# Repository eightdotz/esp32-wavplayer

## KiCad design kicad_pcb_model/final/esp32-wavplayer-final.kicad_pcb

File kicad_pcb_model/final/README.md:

# Parts List  
  
# LCSC:  
  
MicroSD Module: JBL JBL-102010052 | 9 pin SD card (one detect pin)  
Display: Wise Vision X096-2864KSWPG01-H30 | SSD1315 Display Driver  
Audio Driver: TI PCM5102APWR  
Voltage Regulator for Display: XC6206P332MR-G  
Buttons: OMRON B3U-1000P | SMD buttons  
Battery Controller: TP4096 | 1a of charging current is fine for this application.  
For higher current charging, try the Consonance CN3791  
  
Audio Jack: KHE PJ-332A-6A  
  
# DigiKey:  
  
USB-C Jack: 2223-UJ20-C-H-G-SMT-1-P16-TRCT-ND | 16 pin USB-C port. 2073-USB4125-GF-ACT-ND is the 6 pin alternative  
CPU: ESP32-C3 (1904-ESP32-C3CT-ND)

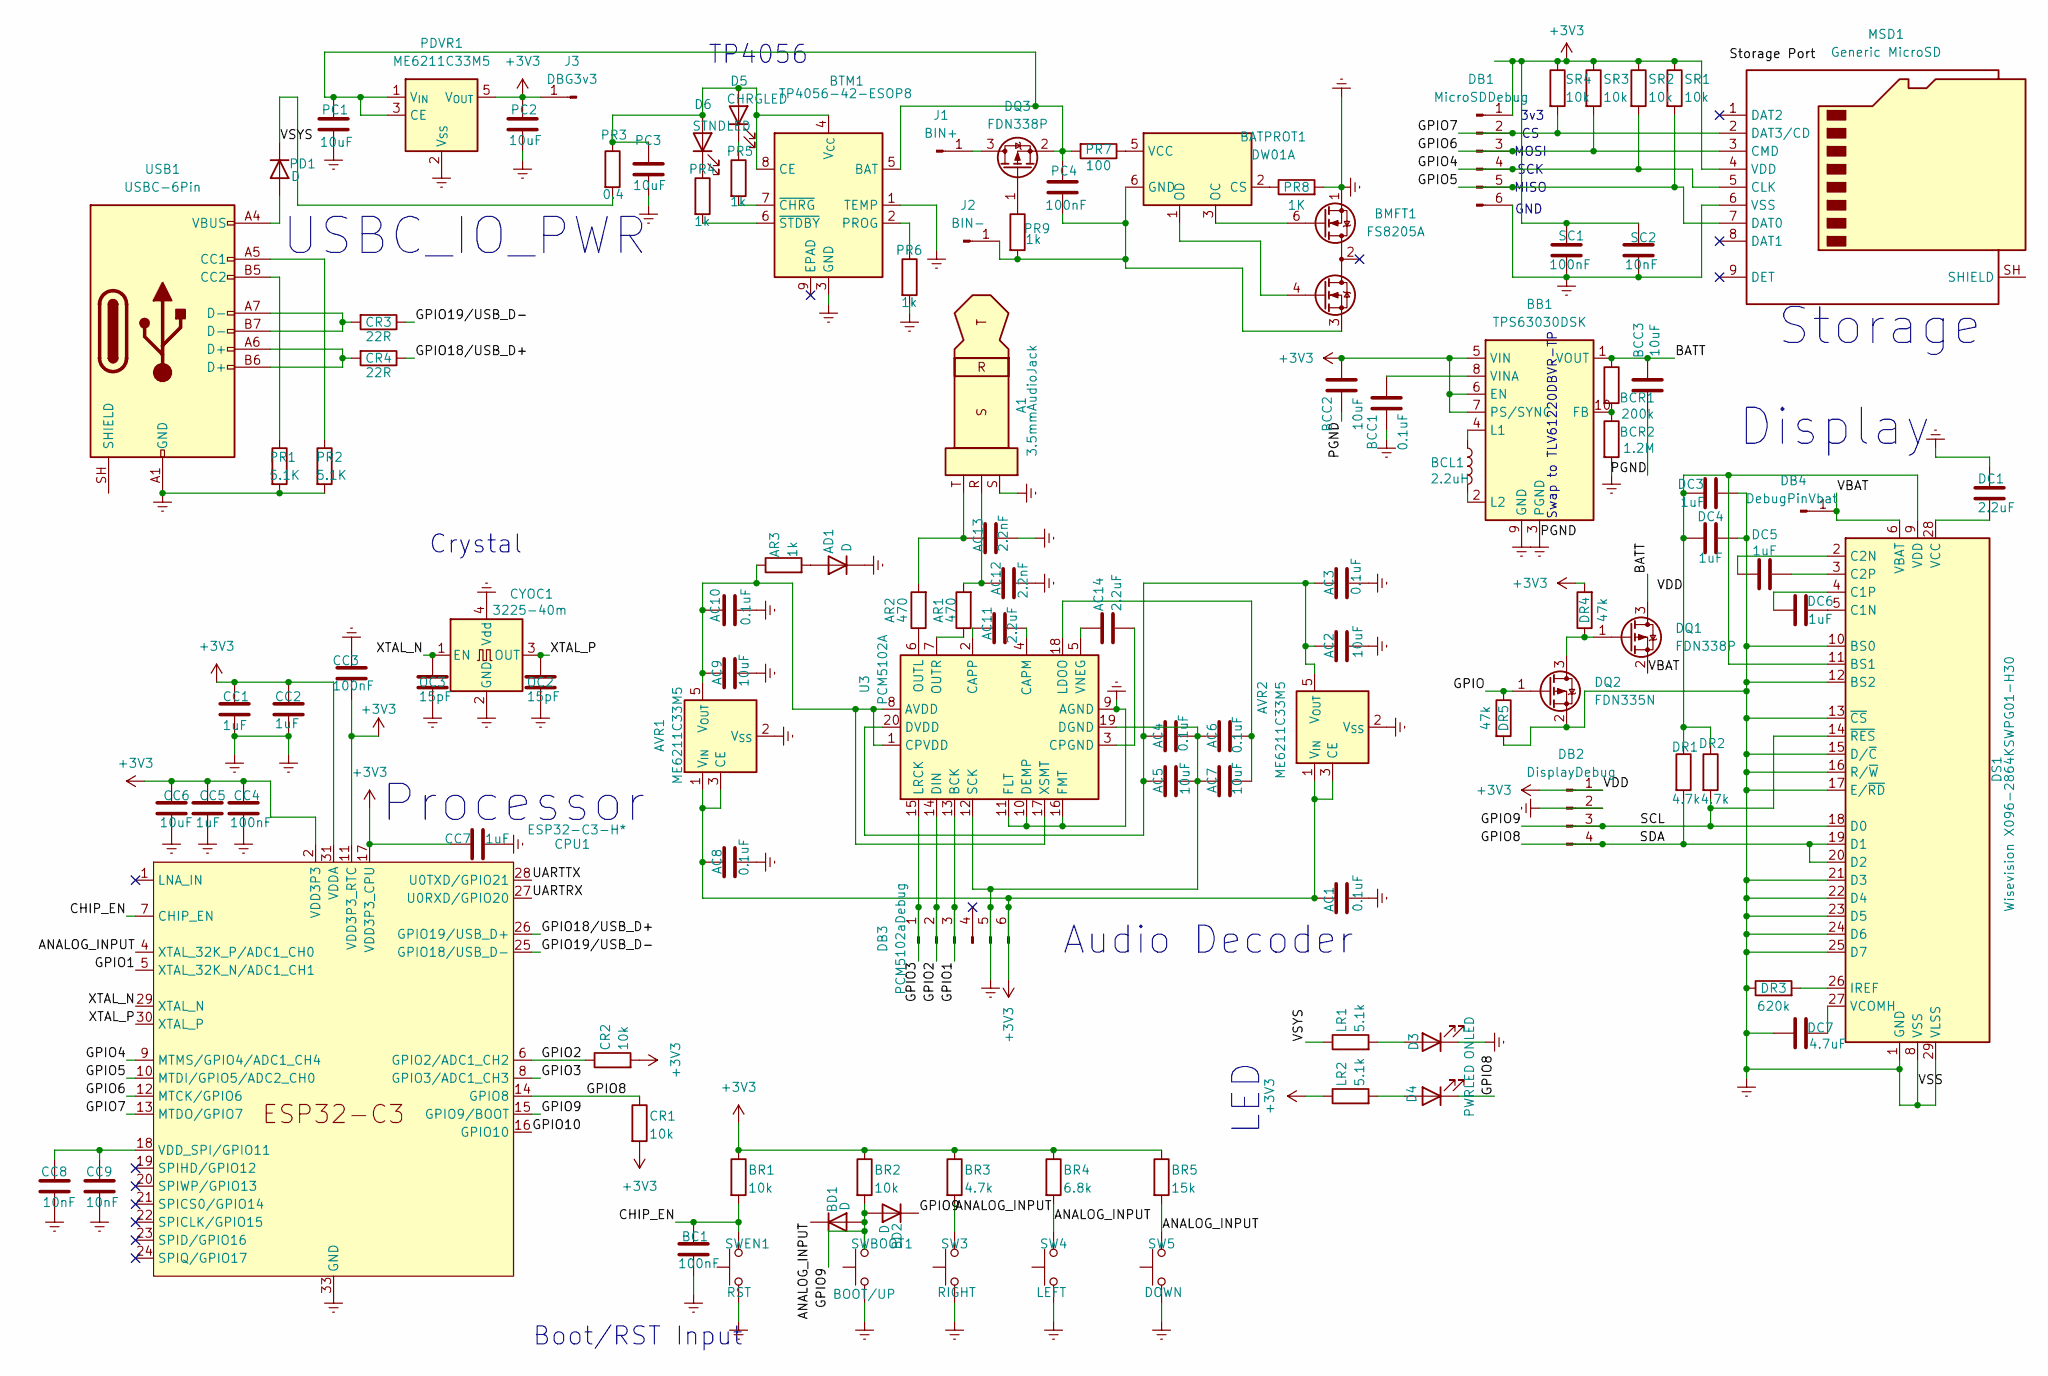
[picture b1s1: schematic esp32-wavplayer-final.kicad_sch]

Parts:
A1: 3.5mmAudioJack; Jack_3.5mm_KoreanHropartsElec_PJ-320D-4A_Horizontal
AC1, AC3, AC4, AC6, AC8, AC10: 0.1uF; C_0603_1608Metric_Pad1.08x0.95mm_HandSolder
AC2, AC5, AC7, AC9: 10uF; C_0603_1608Metric_Pad1.08x0.95mm_HandSolder
AC11, AC14: 2.2uF; C_0603_1608Metric_Pad1.08x0.95mm_HandSolder
AC12, AC13: 2.2nF; C_0603_1608Metric_Pad1.08x0.95mm_HandSolder
AD1: D; D_0603_1608Metric_Pad1.05x0.95mm_HandSolder
AR1, AR2: 470; R_0603_1608Metric_Pad0.98x0.95mm_HandSolder
AR3: 1k; R_0603_1608Metric_Pad0.98x0.95mm_HandSolder
AVR1, AVR2: ME6211C33M5; SOT-23-5
BATPROT1: DW01A; SOT-23-6
BB1: TPS63030DSK; WSON-10-1EP_2.5x2.5mm_P0.5mm_EP1.2x2mm
BC1: 100nF; C_0603_1608Metric_Pad1.08x0.95mm_HandSolder
BCC1: 0.1uF; C_0603_1608Metric_Pad1.08x0.95mm_HandSolder
BCC2, BCC3: 10uF; C_0603_1608Metric_Pad1.08x0.95mm_HandSolder
BCL1: 2.2uH; L_0201_0603Metric_Pad0.64x0.40mm_HandSolder
BCR1: 200k; R_0603_1608Metric_Pad0.98x0.95mm_HandSolder
BCR2: 1.2M; R_0603_1608Metric_Pad0.98x0.95mm_HandSolder
BD1, BD2: D; D_0603_1608Metric_Pad1.05x0.95mm_HandSolder
BMFT1: FS8205A; SOT-23-6
BR1, BR2: 10k; R_0603_1608Metric_Pad0.98x0.95mm_HandSolder
BR3: 4.7k; R_0603_1608Metric_Pad0.98x0.95mm_HandSolder
BR4: 6.8k; R_0603_1608Metric_Pad0.98x0.95mm_HandSolder
BR5: 15k; R_0603_1608Metric_Pad0.98x0.95mm_HandSolder
BTM1: TP4056-42-ESOP8; SOIC-8_3.9x4.9mm_P1.27mm
CC1, CC2, CC5, CC7: 1uF; C_0603_1608Metric_Pad1.08x0.95mm_HandSolder
CC3, CC4: 100nF; C_0603_1608Metric_Pad1.08x0.95mm_HandSolder
CC6: 10uF; C_0603_1608Metric_Pad1.08x0.95mm_HandSolder
CC8, CC9: 10nF; C_0603_1608Metric_Pad1.08x0.95mm_HandSolder
CPU1: ESP32-C3-H*; QFN-32-1EP_5x5mm_P0.5mm_EP3.45x3.45mm
CR1, CR2: 10k; R_0603_1608Metric_Pad0.98x0.95mm_HandSolder
CR3, CR4: 22R; R_0603_1608Metric_Pad0.98x0.95mm_HandSolder
CYOC1: 3225-40m; Oscillator_SMD_Abracon_ASE-4Pin_3.2x2.5mm
D3: PWRLED; LED_0603_1608Metric_Pad1.05x0.95mm_HandSolder
D4: ONLED; LED_0603_1608Metric_Pad1.05x0.95mm_HandSolder
D5: CHRGLED; LED_0603_1608Metric_Pad1.05x0.95mm_HandSolder
D6: STNDLED; LED_0603_1608Metric_Pad1.05x0.95mm_HandSolder
DB1: MicroSDDebug; PinHeader_1x06_P2.54mm_Vertical
DB2: DisplayDebug; PinHeader_1x04_P2.54mm_Vertical
DB3: PCM5102aDebug; PinHeader_1x06_P2.54mm_Vertical
DB4: DebugPinVbat; PinHeader_1x01_P2.54mm_Vertical
DC1: 2.2uF; C_0603_1608Metric_Pad1.08x0.95mm_HandSolder
DC3, DC4, DC5, DC6: 1uF; C_0603_1608Metric_Pad1.08x0.95mm_HandSolder
DC7: 4.7uF; C_0603_1608Metric_Pad1.08x0.95mm_HandSolder
DQ1, DQ3: FDN338P; SOT-23
DQ2: FDN335N; SOT-23
DR1, DR2: 4.7k; R_0603_1608Metric_Pad0.98x0.95mm_HandSolder
DR3: 620k; R_0603_1608Metric_Pad0.98x0.95mm_HandSolder
DR4, DR5: 47k; R_0603_1608Metric_Pad0.98x0.95mm_HandSolder
DS1: Wisevision X096-2864KSWPG01-H30; OLED-128O064D
J1: BIN+; PinHeader_1x01_P2.54mm_Vertical
J2: BIN-; PinHeader_1x01_P2.54mm_Vertical
J3: DBG3v3; PinHeader_1x01_P2.54mm_Vertical
LR1, LR2: 5.1k; R_0603_1608Metric_Pad0.98x0.95mm_HandSolder
MSD1: Generic MicroSD; microSD_HC_Hirose_DM3AT-SF-PEJM5
OC2, OC3: 15pF; C_0603_1608Metric_Pad1.08x0.95mm_HandSolder
PC1, PC2, PC3: 10uF; C_0603_1608Metric_Pad1.08x0.95mm_HandSolder
PC4: 100nF; C_0603_1608Metric_Pad1.08x0.95mm_HandSolder
PD1: D; D_0603_1608Metric_Pad1.05x0.95mm_HandSolder
PDVR1: ME6211C33M5; SOT-23-5
PR1, PR2: 5.1K; R_0603_1608Metric_Pad0.98x0.95mm_HandSolder
PR3: 0.4; R_0603_1608Metric_Pad0.98x0.95mm_HandSolder
PR4, PR5, PR6, PR9: 1k; R_0603_1608Metric_Pad0.98x0.95mm_HandSolder
PR7: 100; R_0603_1608Metric_Pad0.98x0.95mm_HandSolder
PR8: 1K; R_0603_1608Metric_Pad0.98x0.95mm_HandSolder
SC1: 100nF; C_0603_1608Metric_Pad1.08x0.95mm_HandSolder
SC2: 10nF; C_0603_1608Metric_Pad1.08x0.95mm_HandSolder
SR1, SR2, SR3, SR4: 10k; R_0603_1608Metric_Pad0.98x0.95mm_HandSolder
SW3: RIGHT; SW_SPST_TS-1088-xR020
SW4: LEFT; SW_SPST_TS-1088-xR020
SW5: DOWN; SW_SPST_TS-1088-xR020
SWBOOT1: BOOT/UP; SW_SPST_TS-1088-xR020
SWEN1: RST; SW_SPST_TS-1088-xR020
U3: PCM5102A; TSSOP-20_4.4x6.5mm_P0.65mm
USB1: USBC-6Pin; USB_C_Receptacle_HRO_TYPE-C-31-M-12

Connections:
+3V3: AC1.1, AC8.1, AVR1.1 (V_{IN}), AVR1.3 (CE), AVR2.1 (V_{IN}), AVR2.3 (CE), BB1.5 (VIN), BB1.6 (EN), BB1.7 (PS/SYNC), BCC2.2, BR1.1, BR2.1, BR3.1, BR4.1, BR5.1, CC1.1, CC2.1, CC3.2, CC4.1, CC5.1, CC6.1, CC7.1, CPU1.2 (VDD3P3), CPU1.3 (VDD3P3), CPU1.11 (VDD3P3_RTC), CPU1.17 (VDD3P3_CPU), CPU1.31 (VDDA), CPU1.32 (VDDA), CR1.2, CR2.2, DB1.1, DB2.1, DB3.6, DC3.1, DC4.2, DR1.1, DR2.1, DR4.2, DS1.9 (VDD), DS1.11 (BS1), J3.1 (Pin_1_1), LR2.1, MSD1.4 (VDD), PC2.1, PDVR1.5 (V_{OUT}), SC1.1, SC2.1, SR1.1, SR2.1, SR3.1, SR4.1
/ANALOG_INPUT: BD1.1 (K), BR3.2, BR4.2, BR5.2, CPU1.4 (XTAL_32K_P/ADC1_CH0), SW3.2, SW4.2, SW5.2
/BATT: BB1.1 (VOUT), BCC3.2, BCR1.1, DQ1.3 (D)
/CHIP_EN: BC1.1, BR1.2, CPU1.7 (CHIP_EN), SWEN1.2; also elsewhere on the board
/GPIO: DQ2.1 (G), DR5.1
/GPIO1: CPU1.5 (XTAL_32K_N/ADC1_CH1), DB3.3, U3.13 (BCK)
/GPIO2: CPU1.6 (GPIO2/ADC1_CH2), CR2.1, DB3.2, U3.14 (DIN)
/GPIO3: CPU1.8 (GPIO3/ADC1_CH3), DB3.1, U3.15 (LRCK)
/GPIO4: CPU1.9 (MTMS/GPIO4/ADC1_CH4), DB1.4, MSD1.5 (CLK), SR2.2
/GPIO5: CPU1.10 (MTDI/GPIO5/ADC2_CH0), DB1.5, MSD1.7 (DAT0), SR1.2
/GPIO6: CPU1.12 (MTCK/GPIO6), DB1.3, MSD1.3 (CMD), SR3.2
/GPIO7: CPU1.13 (MTDO/GPIO7), DB1.2, MSD1.2 (DAT3/CD), SR4.2
/GPIO8: CPU1.14 (GPIO8), CR1.1, D4.1 (K), DB2.4, DR1.2, DS1.19 (D1), DS1.20 (D2)
/GPIO10: CPU1.16 (GPIO10)
/GPIO18/USB_D+: CPU1.26 (GPIO19/USB_D+), CR4.1
/GPIO19/USB_D-: CPU1.25 (GPIO18/USB_D-), CR3.1
/UARTRX: CPU1.27 (U0RXD/GPIO20)
/UARTTX: CPU1.28 (U0TXD/GPIO21)
/VBAT: DB4.1 (Pin_1_1), DQ1.2 (S), DS1.6 (VBAT)
/VSYS: LR1.1, PD1.1 (K), PR3.2
/XTAL_N: CPU1.29 (XTAL_N), CYOC1.1 (EN), OC3.1
/XTAL_P: CPU1.30 (XTAL_P), CYOC1.3 (OUT), OC2.1
Earth: A1.S, AC1.2, AC2.2, AC3.2, AC4.2, AC5.2, AC6.1, AC7.1, AC8.2, AC9.2, AC10.2, AC12.2, AC13.2, AD1.1 (K), AVR1.2 (V_{SS}), AVR2.2 (V_{SS}), BB1.3 (PGND), BB1.9 (GND), BB1.11 (PGND), BC1.2, BCC1.1, BCC2.1, BCC3.1, BCR2.2, BMFT1.1 (D1), BTM1.1 (TEMP), BTM1.3 (GND), CC1.2, CC2.2, CC3.1, CC4.2, CC5.2, CC6.2, CC7.2, CC8.2, CC9.2, CPU1.33 (GND), CYOC1.2 (GND), CYOC1.4 (Vdd), D3.1 (K), DB1.6, DB2.2, DB3.5, DC1.1, DC3.2, DC4.1, DC7.1, DQ2.2 (S), DR3.1, DR5.2, DS1.1 (GND), DS1.8 (VSS), DS1.10 (BS0), DS1.12 (BS2), DS1.13 (~CS), DS1.15 (D/~C), DS1.16 (R/~W), DS1.17 (E/~RD), DS1.21 (D3), DS1.22 (D4), DS1.23 (D5), DS1.24 (D6), DS1.25 (D7), DS1.29 (VLSS), DS1.30 (GND), MSD1.6 (VSS), OC2.2, OC3.2, PC1.2, PC2.2, PC3.2, PDVR1.2 (V_{SS}), PR1.2, PR2.2, PR6.2, PR8.2, SC1.2, SC2.2, SW3.1, SW4.1, SW5.1, SWBOOT1.1, SWEN1.1, U3.9 (AGND), U3.10 (DEMP), U3.11 (FLT), U3.12 (SCK), U3.16 (FMT), U3.19 (DGND), USB1.A1 (GND), USB1.A12 (GND), USB1.B1 (GND), USB1.B12 (GND); also elsewhere on the board
unnamed: A1.R, AC12.1, AR1.2
unnamed: A1.T, AC13.1, AR2.2
unnamed: AD1.2 (A), AR3.2
unnamed: AC9.1, AC10.1, AR3.1, AVR1.5 (V_{OUT}), U3.1 (CPVDD), U3.8 (AVDD), U3.17 (XSMT)
unnamed: AC2.1, AC3.1, AC4.1, AC5.1, AVR2.5 (V_{OUT}), U3.20 (DVDD)
unnamed: BATPROT1.2 (CS), PR8.1
unnamed 29: BATPROT1.6 (GND), BMFT1.3 (S2), J2.1, PC4.2, PR9.2; also elsewhere on the board
unnamed: BATPROT1.3 (OC), BMFT1.6 (G1)
unnamed: BATPROT1.1 (OD), BMFT1.4 (G2)
unnamed: BATPROT1.5 (VCC), PR7.1
unnamed: BB1.10 (FB), BCR1.2, BCR2.1
unnamed: BB1.4 (L1), BCL1.1
unnamed: BB1.2 (L2), BCL1.2
unnamed: BB1.8 (VINA), BCC1.2
unnamed 37: BTM1.5 (BAT), DQ3.2 (S), PC1.1, PC4.1, PDVR1.1 (V_{IN}), PDVR1.3 (CE), PR7.2; also elsewhere on the board
unnamed: BTM1.4 (V_{CC}), BTM1.8 (CE), D5.2 (A), D6.2 (A), PC3.1, PR3.1
unnamed: BTM1.2 (PROG), PR6.1
unnamed: BTM1.7 (~CHRG), PR5.2
unnamed: BTM1.6 (~STDBY), PR4.2
unnamed: CC8.1, CC9.1, CPU1.18 (VDD_SPI/GPIO11)
unnamed: CR3.2, USB1.A7 (D-), USB1.B7 (D-)
unnamed: CR4.2, USB1.A6 (D+), USB1.B6 (D+)
unnamed: D3.2 (A), LR1.2
unnamed: D4.2 (A), LR2.2
unnamed: D5.1 (K), PR5.1
unnamed: D6.1 (K), PR4.1
unnamed: DQ1.1 (G), DQ2.3 (D), DR4.1
unnamed: DQ3.1 (G), PR9.1
unnamed: DQ3.3 (D), J1.1
unnamed: DC6.2, DS1.5 (C1N)
unnamed: DC6.1, DS1.4 (C1P)
unnamed: DC5.1, DS1.2 (C2N)
unnamed: DC5.2, DS1.3 (C2P)
unnamed: DR3.2, DS1.26 (IREF)
unnamed: DC1.2, DS1.28 (VCC)
unnamed: DC7.2, DS1.27 (VCOMH)
unnamed: PD1.2 (A), USB1.A4 (VBUS), USB1.A9 (VBUS), USB1.B4 (VBUS), USB1.B9 (VBUS)
unnamed: AC11.2, U3.4 (CAPM)
unnamed: AC11.1, U3.2 (CAPP)
unnamed: AC14.2, U3.3 (CPGND)
unnamed: AC6.2, AC7.2, U3.18 (LDOO)
unnamed: AR2.1, U3.6 (OUTL)
unnamed: AR1.1, U3.7 (OUTR)
unnamed: AC14.1, U3.5 (VNEG)
unnamed: PR2.1, USB1.A5 (CC1)
unnamed: PR1.1, USB1.B5 (CC2)

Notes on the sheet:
Display
Storage
Audio Decoder
MOSI
MISO
Crystal
LED
SCK
Processor
USBC_IO_PWR
3v3
GND
TP4056
Boot/RST Input
Swap to TLV61220DBVR-TP

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
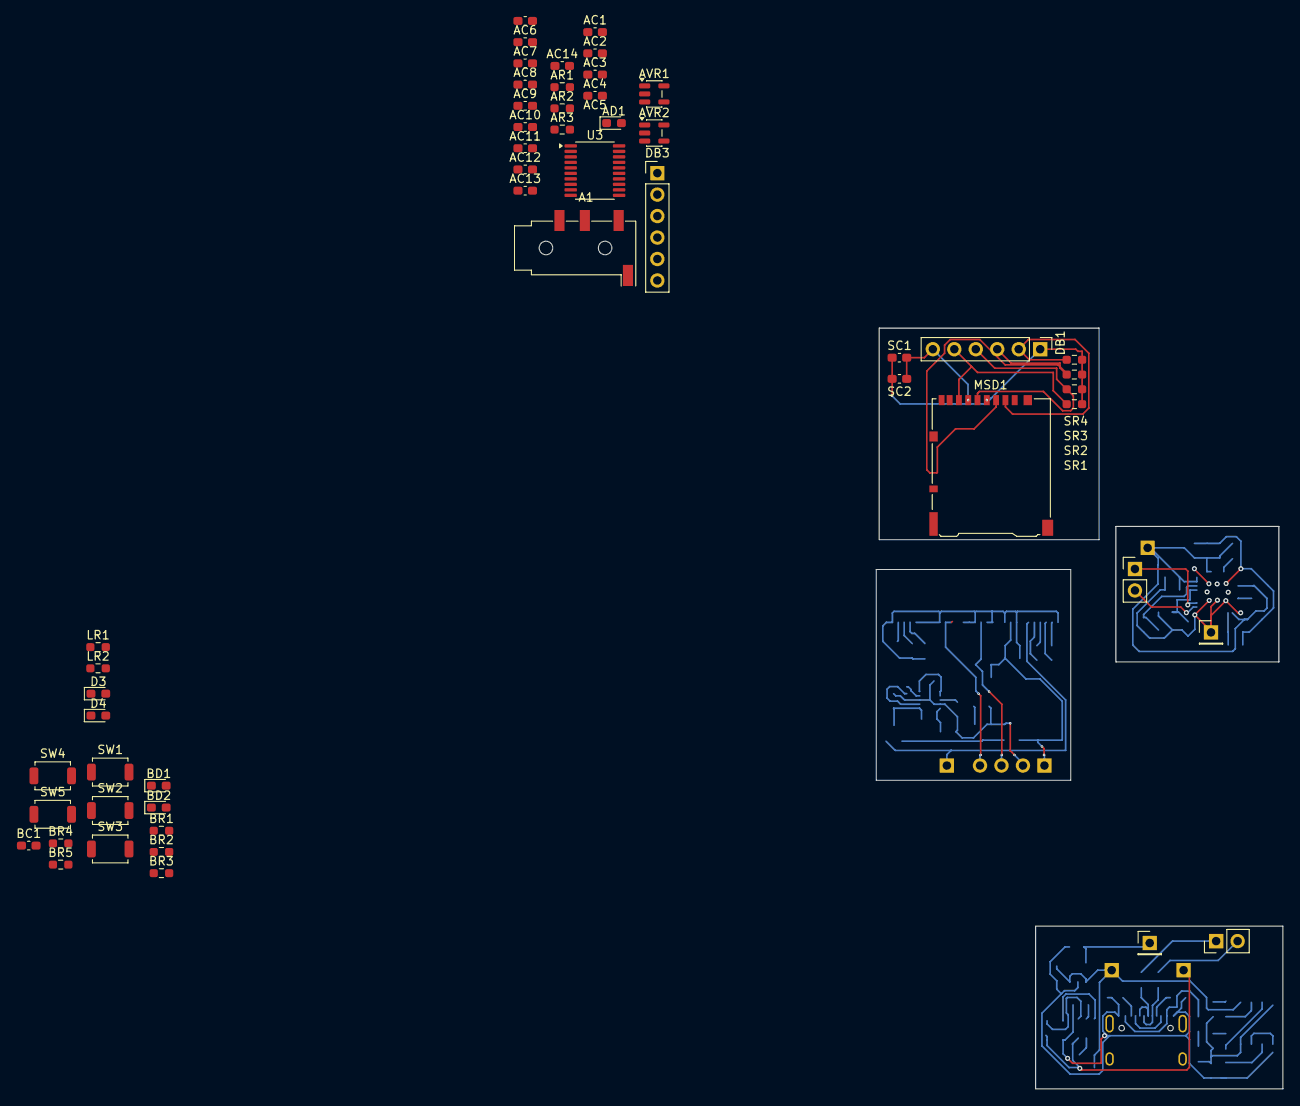
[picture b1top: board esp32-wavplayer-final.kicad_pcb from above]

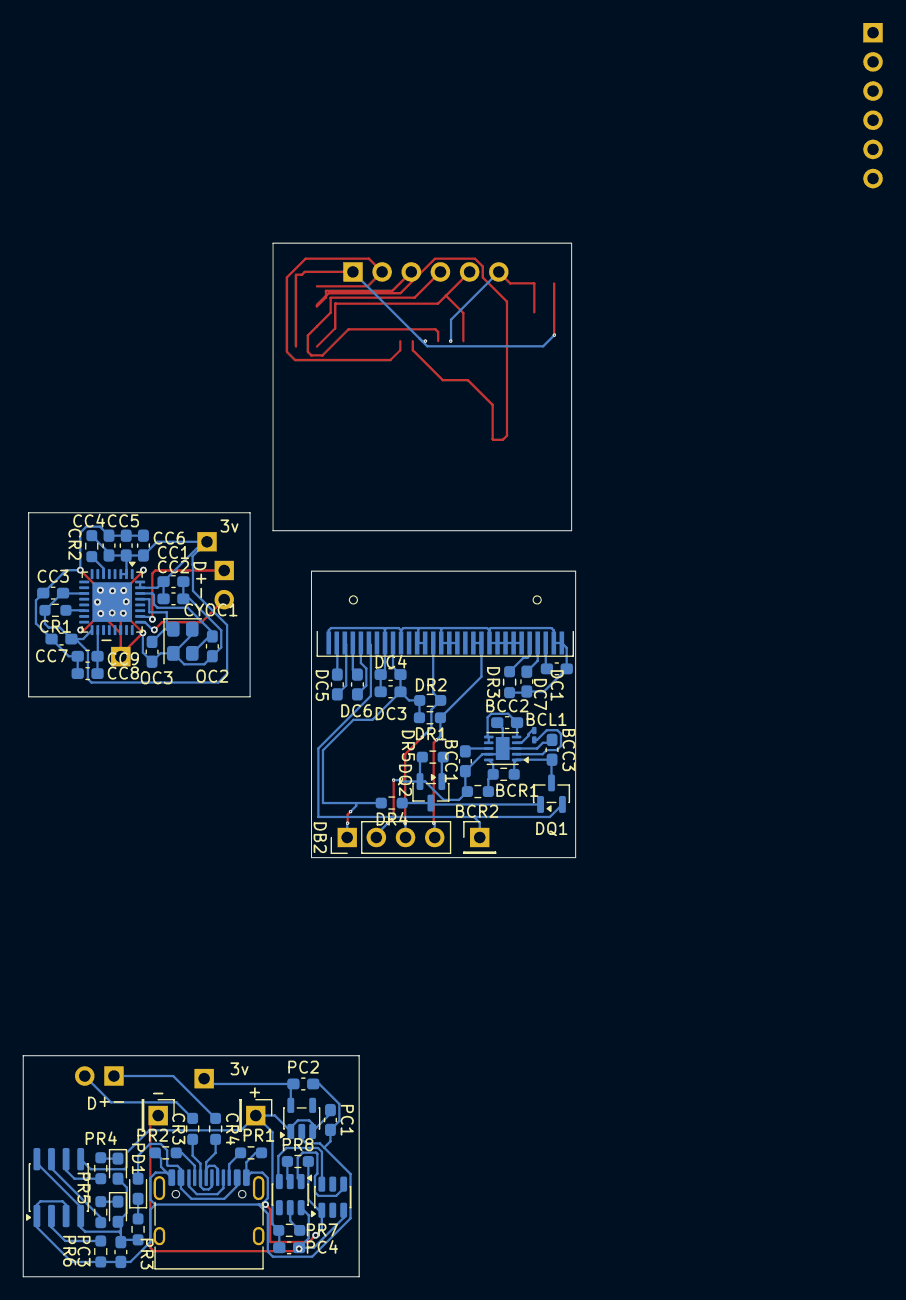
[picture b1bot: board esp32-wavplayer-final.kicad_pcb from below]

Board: 2 copper layers, 48.1 x 90.0 mm, 111 parts (62 on the bottom side), 66 nets.

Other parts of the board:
+: BIN+; PinHeader_1x01_P2.54mm_Vertical
-: BIN-; PinHeader_1x01_P2.54mm_Vertical
SW1: RST; SW_SPST_TS-1088-xR020
SW2: BOOT/UP; SW_SPST_TS-1088-xR020

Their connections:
/CHIP_EN: SW1.2; also elsewhere on the board
Earth: SW1.1, SW2.1; also elsewhere on the board
unnamed 29: -.1 (Pin_1_1); also elsewhere on the board
unnamed 37: +.1 (Pin_1_1); also elsewhere on the board

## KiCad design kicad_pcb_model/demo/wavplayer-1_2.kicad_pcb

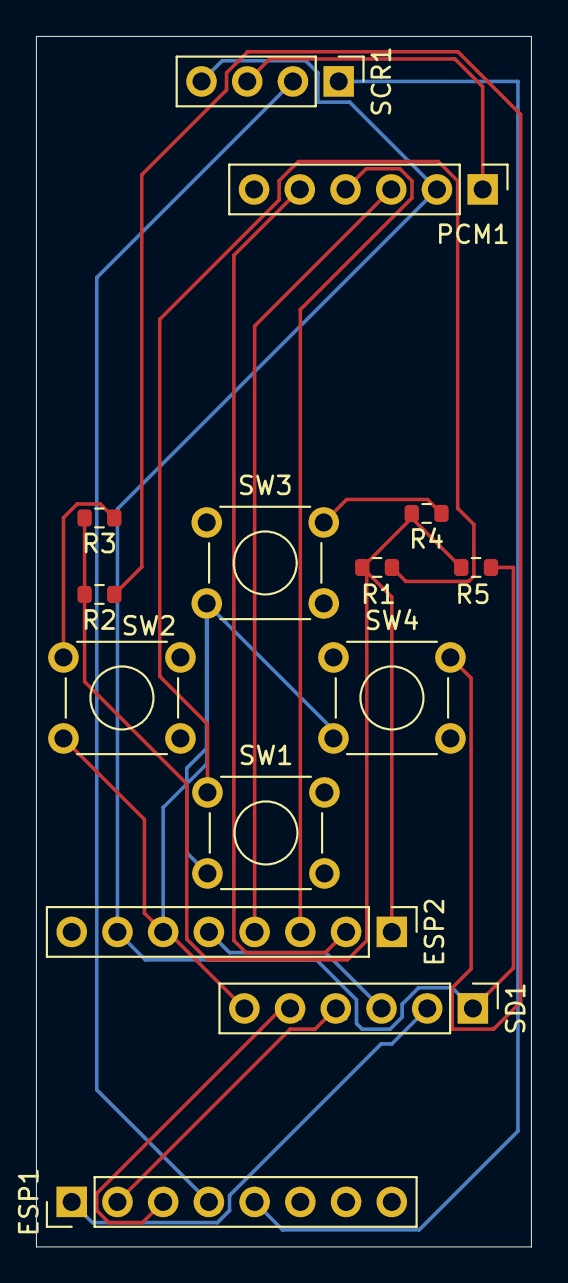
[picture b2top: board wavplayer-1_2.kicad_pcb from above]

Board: 2 copper layers, 27.5 x 67.2 mm, 14 parts (0 on the bottom side), 16 nets.

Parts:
ESP1: ESP32_C3_SuperMini_Right; PinHeader_1x08_P2.54mm_Vertical
ESP2: ESP32_C3_SuperMini_Left; PinHeader_1x08_P2.54mm_Vertical
PCM1: PCM5102a_Genaric; PinHeader_1x06_P2.54mm_Vertical
R1: 1.5k; R_0603_1608Metric
R2: 5.1k; R_0603_1608Metric
R3: 6.8k; R_0603_1608Metric
R4, R5: 10k; R_0603_1608Metric
SCR1: SSD1306; PinHeader_1x04_P2.54mm_Vertical
SD1: SDcard_Generic; PinHeader_1x06_P2.54mm_Vertical
SW1: DOWN; SW_TH_Tactile_Omron_B3F-100x
SW2: BACK; SW_TH_Tactile_Omron_B3F-100x
SW3: UP; SW_TH_Tactile_Omron_B3F-100x
SW4: ENTER; SW_TH_Tactile_Omron_B3F-100x

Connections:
+3V3: ESP2.6, PCM1.1, SCR1.3, SD1.6, SW1.2, SW2.2, SW3.2, SW4.2
/CS: ESP1.3, SD1.5
/GP0_ADC1_0: ESP2.1, R1.2, R2.2, R3.2, R4.2, R5.2
/GP1_ADC1_1: ESP2.2, PCM1.5
/GP2_ADC1_2: ESP2.3, PCM1.4
/GP3_ADC1_3: ESP2.4, PCM1.3
/MISO: ESP1.1, SD1.2
/MOSI: ESP1.2, SD1.4
/SCK: ESP2.5, SD1.3
/SCL: ESP1.4, SCR1.2
/SDA: ESP1.5, SCR1.1
GND: ESP2.7, PCM1.2, R5.1, SCR1.4, SD1.1
unnamed: R1.1, SW1.1
unnamed: R2.1, SW4.1
unnamed: R3.1, SW2.1
unnamed: R4.1, SW3.1
